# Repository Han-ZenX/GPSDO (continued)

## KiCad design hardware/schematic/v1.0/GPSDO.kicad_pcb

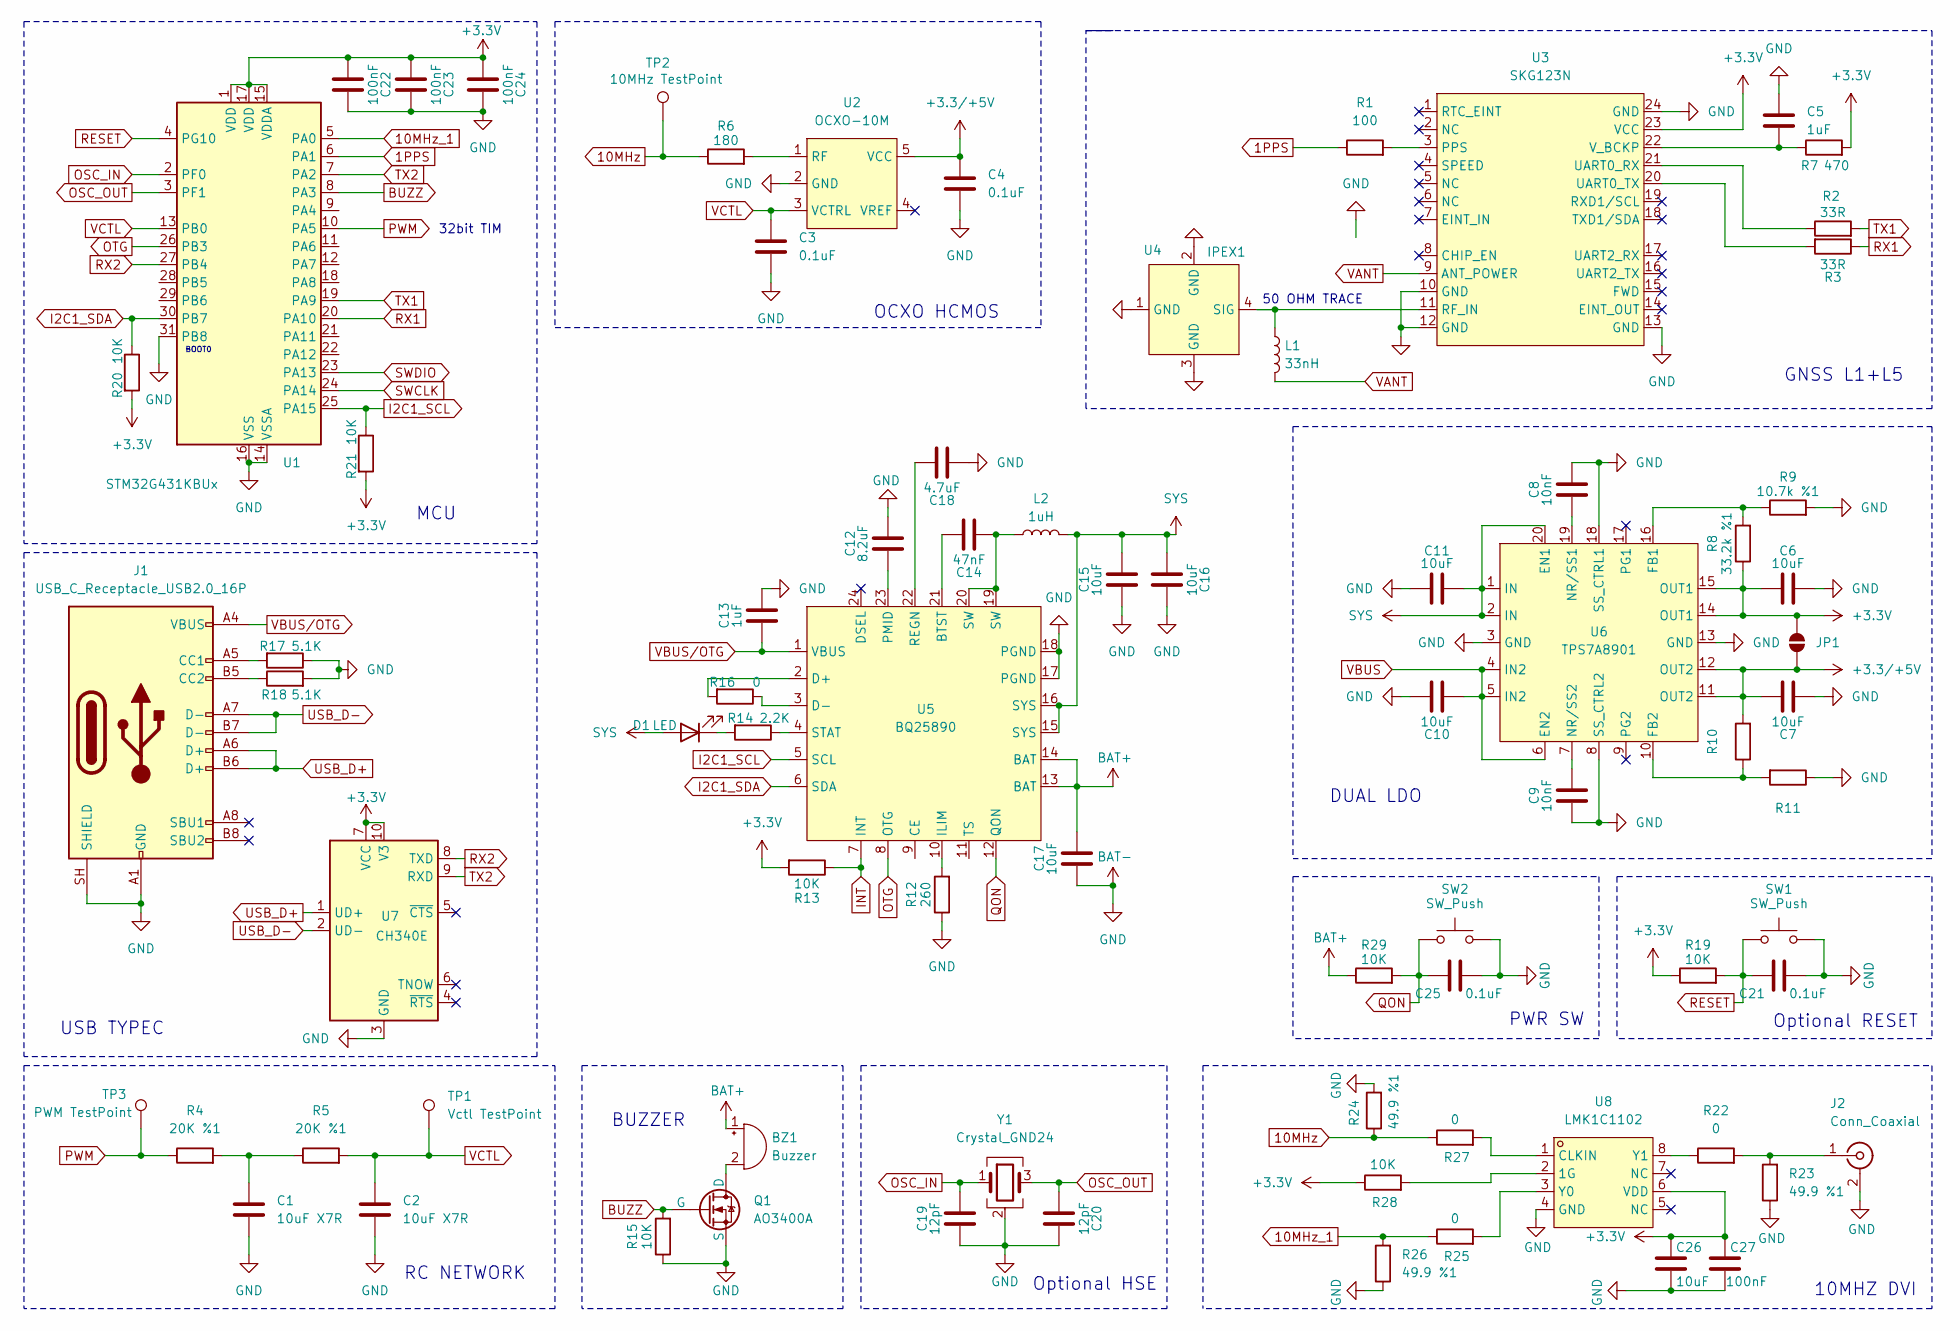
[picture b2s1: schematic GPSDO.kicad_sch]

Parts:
BZ1: Buzzer; BUZ-SMD_L5.0-W5.5-P4.60
C1, C2: 10uF X7R; C_0805_2012Metric
C3, C4: 0.1uF; C_0603_1608Metric
C5, C13: 1uF; C_0603_1608Metric
C6, C7, C10, C11, C15, C16, C17: 10uF; C_0603_1608Metric
C8, C9: 10nF; C_0603_1608Metric
C12: 8.2uF; C_0603_1608Metric
C14: 47nF; C_0603_1608Metric
C18: 4.7uF; C_0603_1608Metric
C19, C20: 12pF; C_0402_1005Metric
C21, C25: 0.1uF; C_0402_1005Metric
C22, C23, C24, C27: 100nF; C_0402_1005Metric
C26: 10uF; C_0402_1005Metric
D1: LED; LED_0603_1608Metric
J1: USB_C_Receptacle_USB2.0_16P; USB_C_Receptacle_G-Switch_GT-USB-7010ASV
J2: Conn_Coaxial; SMA_Amphenol_132289_EdgeMount
JP1: Solder_Jumper2_Open; SolderJumper-2_P1.3mm_Open_Pad1.0x1.5mm
L1: 33nH; L_0603_1608Metric
L2: 1uH; L_0603_1608Metric
Q1: AO3400A; SOT-23-3
R1: 100; R_0402_1005Metric
R2, R3: 33R; R_0402_1005Metric
R4, R5: 20K %1; R_0603_1608Metric
R6: 180; R_0603_1608Metric
R7: 470; R_0402_1005Metric
R8: 33.2k %1; R_0603_1608Metric
R9: 10.7k %1; R_0603_1608Metric
R10, R11: R_0603_1608Metric
R12: 260; R_0603_1608Metric
R13, R15: 10K; R_0603_1608Metric
R14: 2.2K; R_0402_1005Metric
R16, R22, R25, R27: 0; R_0402_1005Metric
R17, R18: 5.1K; R_0402_1005Metric
R19, R20, R21, R28, R29: 10K; R_0402_1005Metric
R23, R24, R26: 49.9 %1; R_0402_1005Metric
SW1, SW2: SW_Push; KEY-SMD_B3U-1000PM
TP1: Vctl TestPoint; Pin_D1.0mm_L10.0mm
TP2: 10MHz TestPoint; Pin_D1.0mm_L10.0mm
TP3: PWM TestPoint; Pin_D1.0mm_L10.0mm
U1: STM32G431KBUx; QFN-32-1EP_5x5mm_P0.5mm_EP3.45x3.45mm
U2: OCXO-10M; OCXO_19x19mm
U3: SKG123N
U4: IPEX1; JLC_IPEX-1
U5: BQ25890; WQFN-24-1EP_4x4mm_P0.5mm_EP2.45x2.45mm
U6: TPS7A8901; QFN-20-1EP_4x4mm_P0.5mm_EP2.5x2.5mm
U7: CH340E; MSOP-10_3x3mm_P0.5mm
U8: LMK1C1102; WSON-8-1EP_2x2mm_P0.5mm_EP0.9x1.6mm
Y1: Crystal_GND24; Crystal_SMD_3225-4Pin_3.2x2.5mm

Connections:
1PPS: R1.1, U1.6 (PA1)
10MHz: R6.1, R24.1, R27.1, TP2.1 (1_1)
10MHz_1: R25.1, R26.2, U1.5 (PA0)
+3.3V: C6.1, C22.1, C23.1, C24.1, C26.1, C27.1, JP1.2 (B), R7.2, R8.1, R13.2, R19.1, R20.2, R21.2, R28.1, U1.1 (VDD), U1.15 (VDDA), U1.17 (VDD), U3.23 (VCC), U6.14 (OUT1), U6.15 (OUT1), U7.7 (VCC), U7.10 (V3), U8.6 (VDD)
+3.3/+5V: C4.1, C7.2, JP1.1 (A), R10.2, U2.5 (VCC), U6.11 (OUT2), U6.12 (OUT2)
BAT+: BZ1.1 (+), C17.2, R29.1, U5.13 (BAT), U5.14 (BAT)
BAT-: C1.2, C2.2, C3.2, C4.2, C5.1, C6.2, C7.1, C8.2, C9.1, C10.2, C11.1, C12.2, C13.2, C15.1, C16.2, C17.1, C18.1, C19.1, C20.2, C21.1, C22.2, C23.2, C24.2, C25.1, C26.2, C27.2, J1.A1 (GND), J1.A12 (GND), J1.B1 (GND), J1.B12 (GND), J1.SH (SHIELD), J2.2 (Ext), Q1.2 (S), R9.2, R11.1, R12.1, R15.1, R17.1, R18.2, R23.1, R24.2, R26.1, SW1.2, SW2.2, U1.14 (VSSA), U1.16 (VSS), U1.31 (PB8), U1.32 (VSS), U1.33 (VSS), U2.2 (GND), U3.10 (GND), U3.12 (GND), U3.13 (GND), U3.24 (GND), U4.1 (GND), U4.2 (GND), U4.3 (GND), U5.17 (PGND), U5.18 (PGND), U6.3 (GND), U6.8 (SS_CTRL2), U6.13 (GND), U6.18 (SS_CTRL1), U7.3 (GND), U8.4 (GND), Y1.2 (G), Y1.4 (G)
BUZZ: Q1.1 (G), R15.2, U1.8 (PA3)
I2C1_SCL: R21.1, U1.25 (PA15), U5.5 (SCL)
I2C1_SDA: R20.1, U1.30 (PB7), U5.6 (SDA)
INT: R13.1, U5.7 (INT)
unnamed: BZ1.2 (-), Q1.3 (D)
unnamed: C1.1, R4.2, R5.1
unnamed: C14.1, L2.1, U5.19 (SW), U5.20 (SW)
unnamed: D1.1 (K), R14.2
unnamed: J1.A5 (CC1), R17.2
unnamed: J1.B5 (CC2), R18.1
unnamed: J2.1 (In), R22.2, R23.2
unnamed: R6.2, U2.1 (RF)
unnamed: R1.2, U3.3 (PPS)
unnamed: L1.1, U3.11 (RF_IN), U4.4 (SIG)
unnamed: R2.1, U3.21 (UART0_RX)
unnamed: R3.2, U3.20 (UART0_TX)
unnamed: C5.2, R7.1, U3.22 (V_BCKP)
unnamed: C14.2, U5.21 (BTST)
unnamed: R16.2, U5.2 (D+)
unnamed: R16.1, U5.3 (D-)
unnamed: R12.2, U5.10 (ILIM)
unnamed: C12.1, U5.23 (PMID)
unnamed: C18.2, U5.22 (REGN)
unnamed: R14.1, U5.4 (STAT)
unnamed: R8.2, R9.1, U6.16 (FB1)
unnamed: R10.1, R11.2, U6.10 (FB2)
unnamed: C8.1, U6.19 (NR/SS1)
unnamed: C9.2, U6.7 (NR/SS2)
unnamed: R28.2, U8.2 (1G)
unnamed: R27.2, U8.1 (CLKIN)
unnamed: R25.2, U8.3 (Y0)
unnamed: R22.1, U8.8 (Y1)
OSC_IN: C19.2, U1.2 (PF0), Y1.1
OSC_OUT: C20.1, U1.3 (PF1), Y1.3
OTG: U1.26 (PB3), U5.8 (OTG)
PWM: R4.1, TP3.1 (1_1), U1.10 (PA5)
QON: C25.2, R29.2, SW2.1, U5.12 (QON)
RESET: C21.2, R19.2, SW1.1, U1.4 (PG10)
RX1: R3.1, U1.20 (PA10)
RX2: U1.27 (PB4), U7.8 (TXD)
SWCLK: U1.24 (PA14)
SWDIO: U1.23 (PA13)
SYS: C11.2, C15.2, C16.1, D1.2 (A), L2.2, U5.15 (SYS), U5.16 (SYS), U6.1 (IN), U6.2 (IN), U6.20 (EN1)
TX1: R2.2, U1.19 (PA9)
TX2: U1.7 (PA2), U7.9 (RXD)
USB_D+: J1.A6 (D+), J1.B6 (D+), U7.1 (UD+)
USB_D-: J1.A7 (D-), J1.B7 (D-), U7.2 (UD-)
VANT: L1.2, U3.9 (ANT_POWER)
VBUS: C10.1, U6.4 (IN2), U6.5 (IN2), U6.6 (EN2)
VBUS/OTG: C13.1, J1.A4 (VBUS), J1.A9 (VBUS), J1.B4 (VBUS), J1.B9 (VBUS), U5.1 (VBUS)
VCTL: C2.1, C3.1, R5.2, TP1.1 (1_1), U1.13 (PB0), U2.3 (VCTRL)

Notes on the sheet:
32bit TIM
MCU
50 OHM TRACE
BUZZER
DUAL LDO
USB TYPEC
Optional HSE
GNSS L1+L5
Optional RESET
BOOT0
PWR SW
OCXO HCMOS
10MHZ DVI
RC NETWORK

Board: 2 copper layers, 76 parts (1 on the bottom side), 56 nets, no tracks yet.

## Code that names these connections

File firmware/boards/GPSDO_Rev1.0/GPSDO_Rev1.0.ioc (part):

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Mcu.Name=STM32G431C(6-8-B)Ux
Mcu.Package=UFQFPN48
Mcu.UserName=STM32G431CBUx
PA1.GPIOParameters=GPIO_Label
PA1.GPIO_Label=VCTL
PA1.Mode=IN2-Single-Ended
PA1.Signal=ADC1_IN2
PA10.Mode=Asynchronous
PA10.Signal=USART1_RX
PA12.GPIOParameters=GPIO_Label
PA12.GPIO_Label=PWM
PA12.Signal=S_TIM4_CH2
PA13.GPIOParameters=GPIO_Label
PA13.GPIO_Label=SWDIO
PA13.Mode=Serial_Wire
PA13.Signal=SYS_JTMS-SWDIO
PA14.GPIOParameters=GPIO_Label
PA14.GPIO_Label=SWCLK
PA14.Mode=Serial_Wire
PA14.Signal=SYS_JTCK-SWCLK
PA15.GPIOParameters=GPIO_Label
PA15.GPIO_Label=TMP_SCL
PA15.Mode=I2C
PA15.Signal=I2C1_SCL
PA2.Mode=Asynchronous
PA2.Signal=USART2_TX
PA3.Mode=Asynchronous
PA3.Signal=USART2_RX
PA4.GPIOParameters=GPIO_Label
PA4.GPIO_Label=TDC_SPI1_NSS
PA4.Mode=NSS_Signal_Hard_Output
PA4.Signal=SPI1_NSS
PA5.GPIOParameters=GPIO_Label
PA5.GPIO_Label=TDC_SPI1_SCK
PA5.Mode=Full_Duplex_Master
PA5.Signal=SPI1_SCK
PA6.GPIOParameters=GPIO_Label
PA6.GPIO_Label=TDC_SPI1_MISO
PA6.Mode=Full_Duplex_Master
PA6.Signal=SPI1_MISO
PA7.GPIOParameters=GPIO_Label
PA7.GPIO_Label=TDC_SPI1_MOSI
PA7.Mode=Full_Duplex_Master
PA7.Signal=SPI1_MOSI
PA9.Mode=Asynchronous
PA9.Signal=USART1_TX
PB0.GPIOParameters=GPIO_Label
PB0.GPIO_Label=BOOST_EN
PB0.Signal=GPIO_Output
PB10.GPIOParameters=GPIO_Label
PB10.GPIO_Label=PULSE_MCU
PB10.Signal=S_TIM2_CH3
PB11.GPIOParameters=GPIO_Label
PB11.GPIO_Label=PULSE_GNSS
PB11.Signal=S_TIM2_CH4
PB3.GPIOParameters=GPIO_Label
PB3.GPIO_Label=LED_RED
PB3.Signal=GPIO_Output
PB7.GPIOParameters=GPIO_Label
PB7.GPIO_Label=TMP_SDA
PB7.Mode=I2C
PB7.Signal=I2C1_SDA
PC10.GPIOParameters=GPIO_Label
PC10.GPIO_Label=LED_GREEN
PC10.Signal=GPIO_Output
PC11.GPIOParameters=GPIO_Label
PC11.GPIO_Label=LED_YELLOW
PC11.Signal=GPIO_Output
PC4.GPIOParameters=GPIO_Label
PC4.GPIO_Label=LED_RED
PC4.Signal=GPIO_Output
PF0-OSC_IN.Mode=HSE-External-Clock-Source
PF0-OSC_IN.Signal=RCC_OSC_IN
RCC.HSE_VALUE=10000000
RCC.SYSCLKFreq_VALUE=170000000
RCC.SYSCLKSource=RCC_SYSCLKSOURCE_PLLCLK
board=custom
